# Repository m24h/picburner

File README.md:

# picburner
a JDM/icprog/ponyprog compatible/modified hardware for burning PICs and other I2C SPI devices.

features:

1. With USB interface.
2. Using a charge pump to provide high voltage for programming, no other power supply needed.
3. Similar logic as JDM/SI-Prog hardware, Compatible with icprog/ponyprog software
4. ICSP compatible connector with modified signal for I2C/SPI devices burning
5. Compatible with 3.3V/5V devices
6. Providing several commonly used programming voltage, and current-limited VPP ouput for clamping outside
7. Circuit is very simple for DIY

issues:

1. I don't know why icprog failed in reading/writing 93CXX devices but ponyprog succeeds

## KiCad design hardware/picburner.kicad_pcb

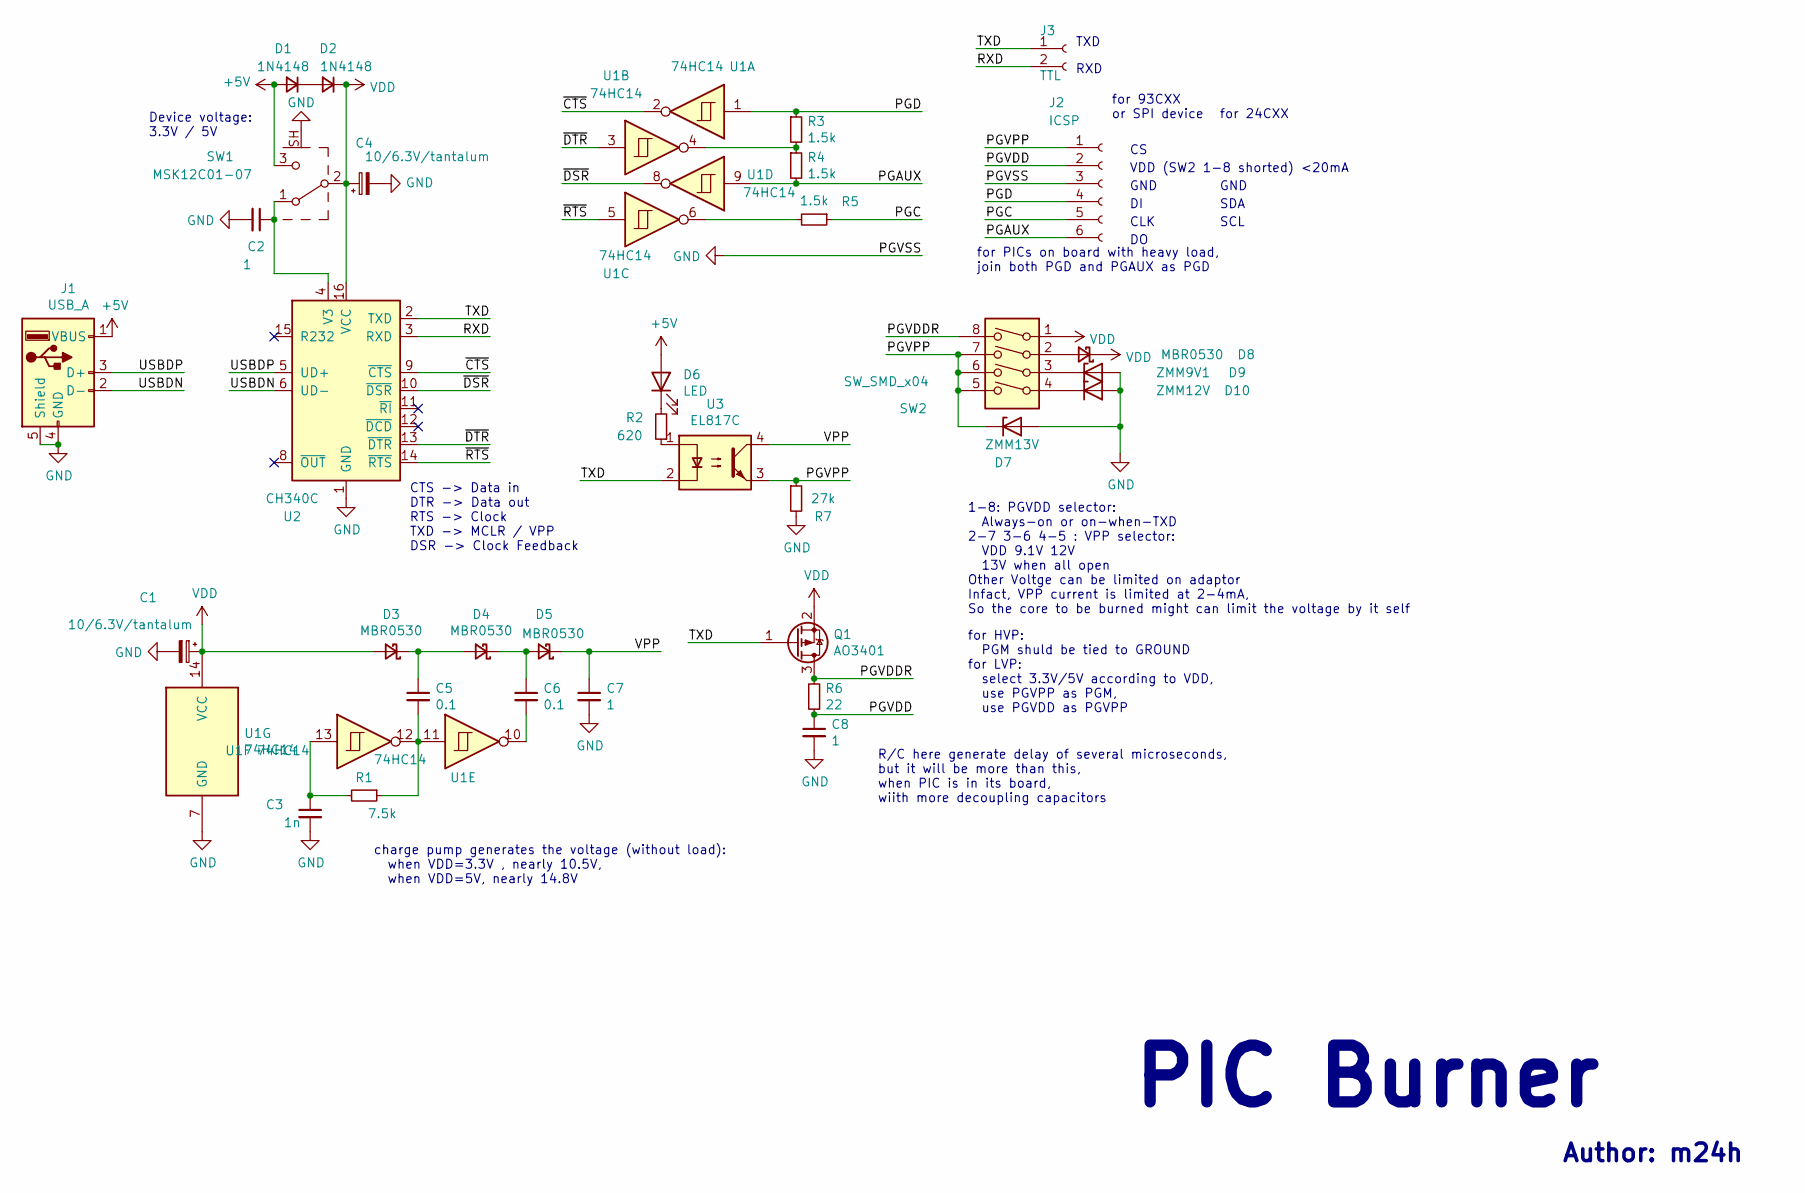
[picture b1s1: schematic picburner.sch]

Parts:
C1, C4: 10/6.3V/tantalum; C_1206_3216Metric
C2, C7, C8: 1; C_0603_1608Metric
C3: 1n; C_0603_1608Metric
C5, C6: 0.1; C_0603_1608Metric
D1, D2: 1N4148; D_SOD-123
D3, D4, D5, D8: MBR0530; D_SOD-123
D6: LED; LED_0805_2012Metric
D7: ZMM13V; D_1206_3216Metric_Castellated
D9: ZMM9V1; D_1206_3216Metric_Castellated
D10: ZMM12V; D_1206_3216Metric_Castellated
J1: USB_A; USB_A_CNCTech_1001-011-01101_Horizontal
J2: ICSP; PinHeader_1x06_P2.54mm_Horizontal
J3: TTL; 2PAD_1x02_P2.54mm_SMD
Q1: AO3401; SOT-23
R1: 7.5k; R_0603_1608Metric
R2: 620; R_0603_1608Metric
R3, R4, R5: 1.5k; R_0603_1608Metric
R6: 22; R_0805_2012Metric
R7: 27k; R_0603_1608Metric
SW1: MSK12C01-07
SW2: SW_SMD_x04; DIP-8_W8.89mm_SMDSocket_LongPads
U1: 74HC14; SOIC-14_3.9x8.7mm_P1.27mm
U2: CH340C; SOP-16_4.4x10.4mm_P1.27mm
U3: EL817C; DIP-4_W8.89mm_SMDSocket_LongPads

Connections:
+5V: D1.2 (A), D6.2 (A), J1.1 (VBUS), SW1.3 (C)
/PGAUX: J2.6, R4.2, U1.9
/PGC: J2.5, R5.1
/PGD: J2.4, R3.1, U1.1
/PGVDD: C8.1, J2.2, R6.1
/PGVDDR: Q1.3 (D), R6.2, SW2.8
/PGVPP: D7.1 (K), J2.1, R7.1, SW2.5, SW2.6, SW2.7, U3.3
/RXD: J3.2, U2.3 (RXD)
/TXD: J3.1, Q1.1 (G), U2.2 (TXD), U3.2
/USBDN: J1.2 (D-), U2.6 (UD-)
/USBDP: J1.3 (D+), U2.5 (UD+)
/VPP: C7.1, D5.1 (K), U3.4
/~CTS: U1.2, U2.9 (~CTS)
/~DSR: U1.8, U2.10 (~DSR)
/~DTR: U1.3, U2.13 (~DTR)
/~RTS: U1.5, U2.14 (~RTS)
GND: C1.2, C2.2, C3.2, C4.2, C7.2, C8.2, D7.2 (A), D9.2 (A), D10.2 (A), J1.4 (GND), J1.5 (Shield), J2.3, R7.2, SW1.SH (Shield), U1.7 (GND), U2.1 (GND)
unnamed: C2.1, SW1.1 (A), U2.4 (V3)
unnamed: C3.1, R1.2, U1.13
unnamed: C5.1, D3.1 (K), D4.2 (A)
unnamed: C5.2, R1.1, U1.11, U1.12
unnamed: C6.1, D4.1 (K), D5.2 (A)
unnamed: C6.2, U1.10
unnamed: D1.1 (K), D2.2 (A)
unnamed: D6.1 (K), R2.2
unnamed: D8.2 (A), SW2.2
unnamed: D9.1 (K), SW2.3
unnamed: D10.1 (K), SW2.4
unnamed: R2.1, U3.1
unnamed: R3.2, R4.1, U1.4
unnamed: R5.2, U1.6
VDD: C1.1, C4.1, D2.1 (K), D3.2 (A), D8.1 (K), Q1.2 (S), SW1.2 (B), SW2.1, U1.14 (VCC), U2.16 (VCC)

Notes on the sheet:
CTS -> Data in DTR -> Data out RTS -> Clock TXD -> MCLR / VPP DSR -> Clock Feedback
Device voltage: 3.3V / 5V
1-8: PGVDD selector: Always-on or on-when-TXD 2-7 3-6 4-5 : VPP selector: VDD 9.1V 12V 13V when all open Other Voltge can be limited on adaptor Infact, VPP current is limited at 2-4mA, So the core to be burned might can limit the voltage by it self
for HVP: PGM shuld be tied to GROUND for LVP: select 3.3V/5V according to VDD, use PGVPP as PGM, use PGVDD as PGVPP
PIC Burner
Author: m24h
R/C here generate delay of several microseconds, but it will be more than this, when PIC is in its board, wiith more decoupling capacitors
charge pump generates the voltage (without load): when VDD=3.3V , nearly 10.5V, when VDD=5V, nearly 14.8V
CLK
for 93CXX or SPI device
for 24CXX
GND
VDD (SW2 1-8 shorted) <20mA
SCL
SDA
for PICs on board with heavy load, join both PGD and PGAUX as PGD
TXD
RXD

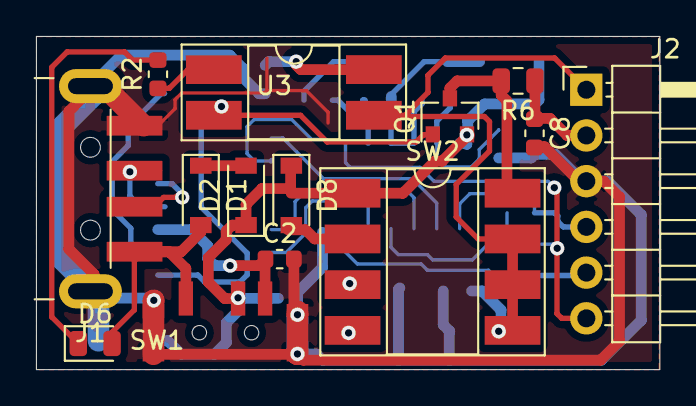
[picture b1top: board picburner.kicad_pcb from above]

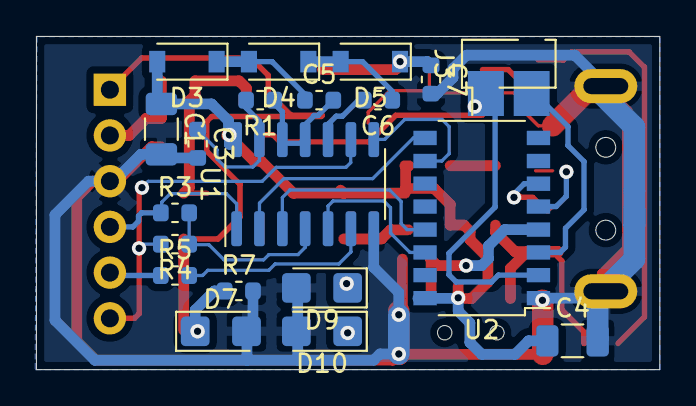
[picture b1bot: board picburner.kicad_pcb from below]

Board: 2 copper layers, 34.6 x 18.5 mm, 34 parts (20 on the bottom side), 32 nets.

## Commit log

2022-01-25 Update README.md
    Brief
2022-01-25 Add files via upload
    First and maybe last version
